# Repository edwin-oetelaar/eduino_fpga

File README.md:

# eduino_fpga
Kicad design experiment for new FPGA board spartan 6.

Part of project with demand-peripherals to bring Eduino.io ecosystem to life. Open source, share alike, you can use it, but must always open your project so everyone can learn from it.

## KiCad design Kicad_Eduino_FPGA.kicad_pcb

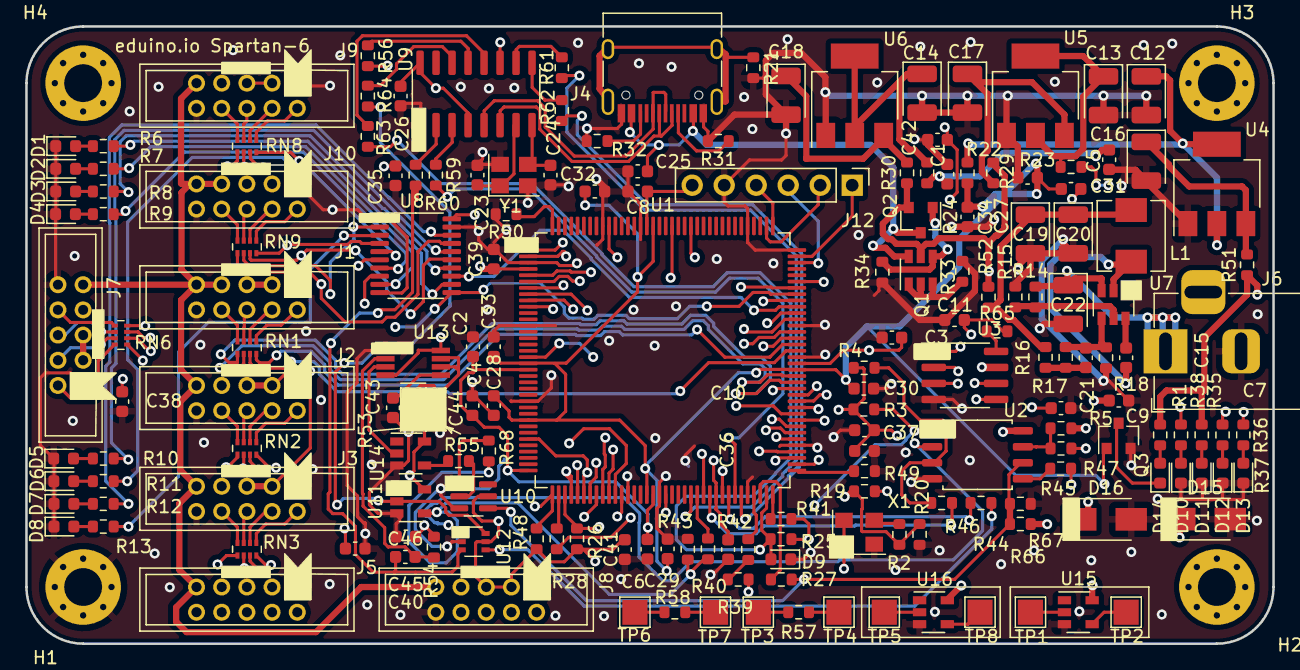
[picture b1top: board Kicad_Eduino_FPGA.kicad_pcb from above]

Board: 4 copper layers, 99.0 x 49.0 mm, 181 parts (0 on the bottom side), 169 nets.

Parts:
C1, C2, C3, C4, C5, C6, C7, C8, C9, C10, C11, C25, C26, C27, C28, C29, C30, C31, C32, C33, C34, C35, C36, C37, C38, C39, C40, C41, C42, C45: 1uF/50V; C_0603_1608Metric
C12, C13, C14, C16, C17, C18, C19, C20, C22: 22uF/16V; CP_EIA-3528-21_Kemet-B
C15: 100n/50V; C_0603_1608Metric
C21: 75pF / 50 V; C_0603_1608Metric
C23, C24: 33pF/50V; C_0603_1608Metric
C43, C44, C46: 1n0/50V; C_0603_1608Metric
D1, D2, D3, D4, D5, D6, D7, D8: LED_Small_RED; LED_0603_1608Metric
D9, D10, D11, D12, D13, D14: GREEN LED 0603; LED_0603_1608Metric
D15, D16: SS14; D_SMA
H1, H2, H3, H4: MountingHole_Pad; MountingHole_3mm_Pad_Via
J1, J2, J3, J5, J7, J8, J9, J10: Conn_02x05_Odd_Even; PinHeader_2x05_P2.00mm_Vertical_edwin
J4: USB_C_Receptacle_USB2.0; USB_C_Receptacle_HRO_TYPE-C-31-M-12
J6: Barrel_Jack_Switch; BarrelJack_Horizontal
J12: Conn_01x06; PinHeader_1x06_P2.54mm_Vertical
L1: 10uH ±20% 3.2A (SMD 5.2 x 5.4 x 3.0 mm); L_Sunlord_MWSA0518_5.4x5.2mm
Q1: Q_DUAL_PNP_PNP_C1B1B2C2E2E1; SOT-23-6
Q2: DMG2305UXQ-7; SOT-23
Q3: DTC143Z; SOT-23
R1, R25, R35, R38: 330R; R_0603_1608Metric
R2, R22, R23, R24, R27, R28, R29, R30, R42, R43, R44, R45, R46, R47, R51, R52, R55, R56, R57, R58, R59, R60, R61, R62, R63, R64, R65, R68: 0R; R_0603_1608Metric
R3, R4, R5, R26, R39, R40, R41, R48, R49, R50: 4k7; R_0603_1608Metric
R6, R7, R8, R9, R10, R11, R12, R13, R36, R37, R53, R54: 1K0; R_0603_1608Metric
R14: 511K / 0603; R_0603_1608Metric
R15: 105K / 0603; R_0603_1608Metric
R16: 49.9 / 0603; R_0603_1608Metric
R17: 100K / 0603; R_0603_1608Metric
R18: 13.3K / 0603; R_0603_1608Metric
R19, R20, R66, R67: 100R; R_0603_1608Metric
R21: 100K; R_0603_1608Metric
R31, R32: 5K1; R_0603_1608Metric
R33: 10K; R_0603_1608Metric
R34: 47K; R_0603_1608Metric
RN1, RN2, RN3, RN6, RN8, RN9: 33R; R_Array_Concave_4x0402
TP1, TP2, TP3, TP4, TP5, TP6, TP7, TP8: TestPoint; TestPoint_Pad_2.0x2.0mm
U1: XC6SLX4-TQG144; TQFP-144_20x20mm_P0.5mm
U2: W25Q128JVSIQ; SOIC-8_5.275x5.275mm_P1.27mm
U3: LY68L6400 (64MBits QSPI); SOIC-8_3.9x4.9mm_P1.27mm
U4: AZ1117-1.2; SOT-223-3_TabPin2
U5, U6: AZ1117-3.3; SOT-223-3_TabPin2
U7: TPS54302DDCR; SOT-23-6
U8: 74HC244; TSSOP-20_4.4x6.5mm_P0.65mm
U9: CH340G; SOIC-16_3.9x9.9mm_P1.27mm
U10: Nexperia 74LVC1G126GV,125; SC-74-6_1.5x2.9mm_P0.95mm
U11, U14, U15, U16: SN74AHC1G04DBVR; SOT-23-5
U12: 74LVC1G157_1; SOT-363_SC-70-6
U13: LMC555CMMX/NOPB; VSSOP-8_3.0x3.0mm_P0.65mm
X1: 20MHz 3225 4P Oscillator; Oscillator_SMD_SeikoEpson_SG8002CE-4Pin_3.2x2.5mm
Y1: 12MHz; Crystal_SMD_3225-4Pin_3.2x2.5mm

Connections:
3V3: C9.1, C10.1, C11.1, C26.1, C35.1, C36.1, C37.1, C38.1, C39.1, C40.1, C41.1, C42.1, C45.1, J1.3, J1.5, J2.3, J2.5, J3.3, J3.5, J5.3, J5.5, J7.3, J7.5, J8.3, J8.5, J9.3, J9.5, J10.3, J10.5, R1.1, R3.1, R4.1, R5.1, R19.1, R23.2, R26.1, R48.1, R53.1, R54.1, R65.2, R66.1, U1.4 (VCCO_3), U1.18 (VCCO_3), U1.31 (VCCO_3), U1.42 (VCCO_2), U1.63 (VCCO_2), U1.76 (VCCO_1), U1.86 (VCCO_1), U1.103 (VCCO_1), U1.122 (VCCO_0), U1.125 (VCCO_0), U1.135 (VCCO_0), U2.8 (VCC), U8.20 (VCC), U9.4 (V3), U9.16 (VCC), U10.5 (VCC), U11.5 (VCC), U12.5 (VCC), U13.4 (R), U13.8 (VCC), U14.5 (VCC), U15.5 (VCC), U16.5 (VCC), X1.1 (~ST), X1.4 (VCC)
5V0: D15.1 (K), J1.7, J1.9, J2.7, J2.9, J3.7, J3.9, J5.7, J5.9, J7.7, J7.9, J8.7, J8.9, J9.7, J9.9, J10.7, J10.9, Q1.5 (E2), Q2.2 (S), R29.1, R30.1, R37.1, R52.2
BOOTMUX: R64.2, U11.2, U12.6 (S)
CMPCS_B_2: R41.2, U1.72 (CMPCS_B_2)
CSO_B_2: R3.2, R28.1, U2.1 (~CS)
CTS: R62.2, U1.67 (IO_L2P_CMPCLK_2)
DIN: R44.1, U12.4 (Y)
DONE_2: D9.2 (A), R25.2, R63.2, U1.71 (DONE_2)
DSR: R61.2, U1.59 (IO_L13N_D10_2)
FLASH_D0: R45.1, U2.5 (DI(IO0))
FLASH_D1: U2.2 (DO(IO1)), U12.1 (IN1)
FLASH_D2: R4.2, R46.1, U2.3 (IO2)
FLASH_D3: R5.2, R47.1, U2.7 (IO3)
FPGA_CCLK: R27.1, R66.2, R67.1, U2.6 (CLK), U10.4
FPGA_M0: R39.2, R42.1
FPGA_M1: R40.1, R43.1, R68.1, U11.4
GND: C1.2, C2.2, C3.2, C4.2, C5.2, C6.2, C7.2, C8.2, C9.2, C10.2, C11.2, C12.2, C13.2, C14.2, C16.2, C17.2, C18.2, C19.2, C20.2, C22.2, C23.2, C24.2, C25.2, C26.2, C27.2, C28.2, C29.2, C30.2, C31.2, C32.2, C33.2, C34.2, C35.2, C36.2, C37.2, C38.2, C39.2, C40.2, C41.2, C42.2, C43.2, C44.2, C45.2, D1.1 (K), D2.1 (K), D3.1 (K), D4.1 (K), D5.1 (K), D6.1 (K), D7.1 (K), D8.1 (K), D9.1 (K), D10.1 (K), D11.1 (K), D12.1 (K), D13.1 (K), D15.2 (A), D16.2 (A), H1.1, J1.1, J1.10, J2.1, J2.10, J3.1, J3.10, J4.A1 (GND), J4.A12 (GND), J4.B1 (GND), J4.B12 (GND), J5.1, J5.10, J6.2, J7.1, J7.10, J8.1, J8.10, J9.1, J9.10, J10.1, J10.10, J12.5, Q3.2 (E), R15.2, R18.2, R20.2, R21.2, R31.2, R32.2, R33.2, R34.2, R40.2, R49.2, R50.2, R67.2, U1.3 (GND), U1.13 (GND), U1.25 (GND), U1.49 (GND), U1.54 (GND), U1.68 (GND), U1.77 (GND), U1.91 (GND), U1.96 (GND), U1.108 (GND), U1.113 (GND), U1.130 (GND), U1.136 (GND), U2.4 (GND), U3.4 (GND), U4.1 (GND), U5.1 (GND), U6.1 (GND), U7.1 (GND), U8.1 (1OE), U8.10 (GND), U8.19 (2OE), U9.1 (GND), U10.3 (GND), U11.3 (GND), U12.2 (GND), U13.1 (GND), U14.3 (GND), U15.3 (GND), U16.3 (GND), X1.2 (GND), Y1.2, Y1.4
HSWAPEN: R50.1, U1.144 (IO_L1P_HSWAPEN_0)
INIT_B_2: R26.2, U1.39 (IO_L65P_INIT_B_2), U9.11 (~RI)
JTAG_TCK: J12.4, U1.109 (TCK)
JTAG_TDI: J12.2, U1.110 (TDI)
JTAG_TDO: J12.3, U1.106 (TDO)
JTAG_TMS: J12.1, U1.107 (TMS)
JTAG_VAUX: C1.1, C2.1, C3.1, C4.1, C5.1, C6.1, C7.1, C8.1, J12.6, R24.2, R25.1, R35.1, R38.1, R39.1, R41.1, R51.1, U1.20 (VCCAUX), U1.36 (VCCAUX), U1.53 (VCCAUX), U1.90 (VCCAUX), U1.129 (VCCAUX)
L32N: RN8.7 (R2.2), U1.101 (IO_L32N_1), U8.11 (2A3)
L32P: RN8.8 (R1.2), U1.102 (IO_L32P_1), U8.8 (1A3)
L33N: RN8.5 (R4.2), U1.99 (IO_L33N_1), U8.13 (2A2)
L33P: RN8.6 (R3.2), U1.100 (IO_L33P_1), U8.6 (1A2)
L34N: RN9.7 (R2.2), U1.97 (IO_L34N_1), U8.15 (2A1)
L34P: RN9.8 (R1.2), U1.98 (IO_L34P_1), U8.4 (1A1)
L40N: RN9.5 (R4.2), U1.94 (IO_L40N_GCLK10_1), U8.17 (2A0)
L40P: RN9.6 (R3.2), U1.95 (IO_L40P_GCLK11_1), U8.2 (1A0)
L41N: RN1.7 (R2.2), U1.92 (IO_L41N_GCLK8_1)
L41P: RN1.8 (R1.2), U1.93 (IO_L41P_GCLK9_IRDY1_1)
L42N: RN1.5 (R4.2), U1.87 (IO_L42N_GCLK6_TRDY1_1)
L42P: RN1.6 (R3.2), U1.88 (IO_L42P_GCLK7_1)
L43N: RN2.7 (R2.2), U1.84 (IO_L43N_GCLK4_1)
L43P: RN2.8 (R1.2), U1.85 (IO_L43P_GCLK5_1)
L45N: RN2.5 (R4.2), U1.82 (IO_L45N_1)
L45P: RN2.6 (R3.2), U1.83 (IO_L45P_1)
L48N: J5.4, U1.47 (IO_L48N_RDWR_B_VREF_2)
L48P: J5.2, U1.48 (IO_L48P_D7_2)
L49N: J5.8, U1.45 (IO_L49N_D4_2)
L49P: J5.6, U1.46 (IO_L49P_D3_2)
L50N: RN3.7 (R2.2), U1.9 (IO_L50N_3)
L50P: RN3.8 (R1.2), U1.10 (IO_L50P_3)
L51N: RN3.5 (R4.2), U1.7 (IO_L51N_3)
L51P: RN3.6 (R3.2), U1.8 (IO_L51P_3)
L52N: RN6.2 (R2.1), U1.5 (IO_L52N_3)
L52P: RN6.1 (R1.1), U1.6 (IO_L52P_3)
L62N: J8.4, U1.43 (IO_L62N_D6_2)
L62P: J8.2, U1.44 (IO_L62P_D5_2)
L64N: J8.8, U1.40 (IO_L64N_D9_2)
L64P: J8.6, U1.41 (IO_L64P_D8_2)
L83N: RN6.4 (R4.1), U1.1 (IO_L83N_VREF_3)
L83P: RN6.3 (R3.1), U1.2 (IO_L83P_3)
unnamed: C12.1, R22.1, U4.2 (VO)
unnamed: C13.1, R23.1, U5.2 (VO)
unnamed: C14.1, R24.1, U6.2 (VO)
unnamed: C15.1, U7.6 (BOOT)
unnamed: C15.2, L1.2, U7.2 (SW)
unnamed: C16.1, R51.2, U4.3 (VI)
unnamed: C17.1, R29.2, U5.3 (VI)
unnamed: C18.1, R30.2, U6.3 (VI)
unnamed: C19.1, C20.1, L1.1, R16.1, R52.1
unnamed: C21.1, R16.2, R17.1
unnamed: C21.2, R17.2, R18.1, U7.4 (FB)
unnamed: C23.1, U9.7 (XI), Y1.1
unnamed: C24.1, U9.8 (XO), Y1.3
unnamed: C43.1, U13.5 (CV)
unnamed: C44.1, R53.2, U13.6 (THR), U13.7 (DIS)
unnamed: C46.2, R54.2, U13.2 (TR)
unnamed: D1.2 (A), R6.2
unnamed: D2.2 (A), R7.2
unnamed: D3.2 (A), R8.2
unnamed: D4.2 (A), R9.2
unnamed: D5.2 (A), R10.2
unnamed: D6.2 (A), R11.2
unnamed: D7.2 (A), R12.2
unnamed: D8.2 (A), R13.2
unnamed: D10.2 (A), R1.2
unnamed: D11.2 (A), R35.2
unnamed: D12.2 (A), R36.2
unnamed: D13.2 (A), R37.2
unnamed: D14.1 (K), Q3.3 (C)
unnamed: D14.2 (A), R38.2
unnamed: J1.2, RN1.1 (R1.1)
unnamed: J1.4, RN1.2 (R2.1)
unnamed: J1.6, RN1.3 (R3.1)
unnamed: J1.8, RN1.4 (R4.1)
unnamed: J2.2, RN2.1 (R1.1)
unnamed: J2.4, RN2.2 (R2.1)
unnamed: J2.6, RN2.3 (R3.1)
unnamed: J2.8, RN2.4 (R4.1)
unnamed: J3.2, RN3.1 (R1.1)
unnamed: J3.4, RN3.2 (R2.1)
unnamed: J3.6, RN3.3 (R3.1)
unnamed: J3.8, RN3.4 (R4.1)
unnamed: J4.A5 (CC1), R31.1
unnamed: J4.A6 (D+), J4.B6 (D+), U9.5 (UD+)
unnamed: J4.A7 (D-), J4.B7 (D-), U9.6 (UD-)
unnamed: J4.B5 (CC2), R32.1
unnamed: J4.S1 (SHIELD), R21.1
unnamed: J7.2, RN6.8 (R1.2)
unnamed: J7.4, RN6.7 (R2.2)
unnamed: J7.6, RN6.6 (R3.2)
unnamed: J7.8, RN6.5 (R4.2)
unnamed: J9.2, RN8.1 (R1.1)
unnamed: J9.4, RN8.2 (R2.1)
unnamed: J9.6, RN8.3 (R3.1)
unnamed: J9.8, RN8.4 (R4.1)
unnamed: J10.2, RN9.1 (R1.1)
unnamed: J10.4, RN9.2 (R2.1)
unnamed: J10.6, RN9.3 (R3.1)
unnamed: J10.8, RN9.4 (R4.1)
unnamed: Q1.1 (C1), Q1.2 (B1), Q1.3 (B2), R33.1
unnamed: Q1.4 (C2), Q2.1 (G), R34.1
unnamed: R2.2, X1.3 (OUT)
unnamed: R6.1, U8.12 (1Y3)
unnamed: R7.1, U8.9 (2Y3)
unnamed: R8.1, U8.14 (1Y2)
unnamed: R9.1, U8.7 (2Y2)
unnamed: R10.1, U8.16 (1Y1)
unnamed: R11.1, U8.5 (2Y1)
unnamed: R12.1, U8.18 (1Y0)
unnamed: R13.1, U8.3 (2Y0)
unnamed: R14.2, R15.1, U7.5 (EN)
unnamed: R27.2, U1.70 (IO_L1P_CCLK_2)
unnamed: R28.2, U1.38 (IO_L65N_CSO_B_2)
unnamed: R42.2, U1.69 (IO_L1N_M0_CMPMISO_2)
unnamed: R43.2, U1.60 (IO_L13P_M1_2)
unnamed: R44.2, U1.65 (IO_L3P_D0_DIN_MISO_MISO1_2)
unnamed: R45.2, U1.64 (IO_L3N_MOSI_CSI_B_MISO0_2)
unnamed: R46.2, U1.62 (IO_L12P_D1_MISO2_2)
unnamed: R47.2, U1.61 (IO_L12N_D2_MISO3_2)
unnamed: R55.1, U14.4
unnamed: R55.2, U10.2
unnamed: R56.1, U9.13 (~DTR)
unnamed: R57.1, TP3.1
unnamed: R57.2, TP4.1
unnamed: R58.1, TP6.1
unnamed: R58.2, TP7.1
unnamed: R59.1, U9.3 (RXD)
unnamed: R60.1, U9.2 (TXD)
unnamed: R61.1, U9.10 (~DSR)
unnamed: R62.1, U9.9 (~CTS)
unnamed: R63.1, U9.12 (~DCD)
unnamed: R64.1, U9.14 (~RTS)
unnamed: R65.1, U3.8 (VCC)
unnamed: R68.2, U10.1
unnamed: TP1.1, U15.2
unnamed: TP2.1, U15.4
unnamed: TP5.1, U16.2
unnamed: TP8.1, U16.4
OUT555: U13.3 (Q), U14.2
PROGRAM_B_2: R48.2, R56.2, U1.37 (PROGRAM_B_2)
RX: R59.2, U1.66 (IO_L2N_CMPMOSI_2)
SPIRAM_CS: U1.74 (IO_L74N_DOUT_BUSY_1), U3.1 (~CS)
SPIRAM_HOLD: U1.75 (IO_L74P_AWAKE_1), U3.7 (~HOLD)
SPIRAM_MISO: U1.80 (IO_L46N_1), U3.2 (MISO)
SPIRAM_MOSI: U1.79 (IO_L47P_1), U3.5 (MOSI)
SPIRAM_SCK: U1.78 (IO_L47N_1), U3.6 (SCK)
SPIRAM_WP: U1.81 (IO_L46P_1), U3.3 (~WP)
SUSPEND: R49.1, U1.73 (SUSPEND)
TRIG_555: C46.1, R60.2, U12.3 (IN0)
USER_CLOCK: R2.1, R19.2, R20.1, U1.55 (IO_L30N_GCLK0_USERCCLK_2)
VINT_1V2: C27.1, C28.1, C29.1, C30.1, C31.1, C32.1, C33.1, C34.1, Q3.1 (B), R22.2, U1.19 (VCCINT), U1.28 (VCCINT), U1.52 (VCCINT), U1.89 (VCCINT), U1.128 (VCCINT)
VUSB: C25.1, J4.A4 (VBUS), J4.A9 (VBUS), J4.B4 (VBUS), J4.B9 (VBUS), Q1.6 (E1), Q2.3 (D), R36.1
V_EXTERN: C22.1, D16.1 (K), J6.1, R14.1, U7.3 (VIN)

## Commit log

2021-02-08 Update README.md
    some vision about openness
2021-02-14 backup working directory. May contain errors or other problems, this is my personal work, no contract implied. Will clean up this project later.
2021-06-11 updating to repo for Bob # Please enter the commit message for your changes. Lines starting # with '#' will be ignored, and an empty message aborts the commit. # # On branch main # Your branch is up 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
